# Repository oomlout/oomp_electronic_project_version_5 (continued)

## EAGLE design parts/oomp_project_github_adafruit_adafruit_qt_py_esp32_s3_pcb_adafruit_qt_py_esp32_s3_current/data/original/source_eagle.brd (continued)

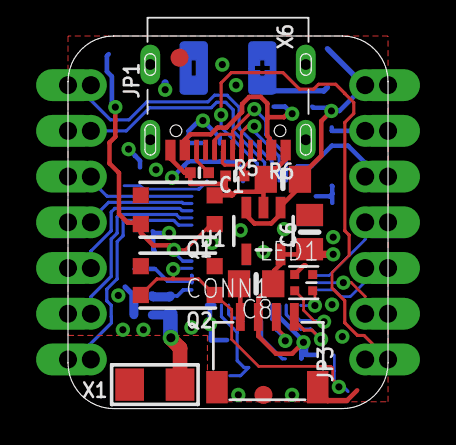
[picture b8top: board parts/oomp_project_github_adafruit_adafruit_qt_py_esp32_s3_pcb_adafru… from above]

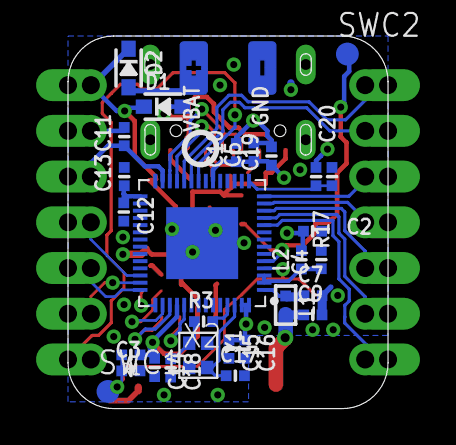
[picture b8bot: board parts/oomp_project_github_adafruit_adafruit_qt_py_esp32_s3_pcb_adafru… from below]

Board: 4 copper layers, 17.8 x 20.7 mm, 49 parts (32 on the bottom side), 34 nets.

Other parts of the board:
U$7: QTPY_ESP32_TOP
U$11: QTPYS3_BOT
U$12: PCBFEAT-REV-040

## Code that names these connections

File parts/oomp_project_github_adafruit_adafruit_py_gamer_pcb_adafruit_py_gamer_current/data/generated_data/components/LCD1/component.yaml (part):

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      connected_to:
      - reference: U$24
        pin_number: '1'
        pin_name: PA00/EINT0/SERCOM1.0
    - number: '7'
      name: RS/DC
      electrical_type: input
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      connected_to:
      - reference: U$24
        pin_number: '6'
        pin_name: PB05/I5/AIN7
    - number: '8'
      name: DATA
      electrical_type: bidirectional
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      connected_to:
      - reference: U$24
        pin_number: '28'
        pin_name: PB15/I15/SERCOM4.3/PCC9
    - number: '9'
      name: CLOCK
      electrical_type: input
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      connected_to:
      - reference: U$24
        pin_number: '26'
        pin_name: PB13/I13/SERCOM4.1/I2SMCK1
    - number: '10'
      name: VCC
      electrical_type: power_in
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      connected_to:
      - reference: U$24
        pin_number: '25'
        pin_name: PB12/I12/SERCOM4.0/I2SCK1
    - number: '13'
      name: GND2
      electrical_type: power_in
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    pin_name: VSS
  - reference: U$24
    pin_number: '1'
    pin_name: PA00/EINT0/SERCOM1.0
  - reference: U$24
    pin_number: '21'
    pin_name: VDDIO_0
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    pin_name: GND_1
  - reference: U$24
    pin_number: '25'
    pin_name: PB12/I12/SERCOM4.0/I2SCK1
  - reference: U$24
    pin_number: '26'
    pin_name: PB13/I13/SERCOM4.1/I2SMCK1
  - reference: U$24
    pin_number: '28'
    pin_name: PB15/I15/SERCOM4.3/PCC9
  - reference: U$24
    pin_number: '33'
    pin_name: GND_2
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    pin_name: VDDIO_3
  - reference: U$24
    pin_number: '6'
    pin_name: PB05/I5/AIN7
  - reference: U$24
    pin_number: '7'
    pin_name: GND_0
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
